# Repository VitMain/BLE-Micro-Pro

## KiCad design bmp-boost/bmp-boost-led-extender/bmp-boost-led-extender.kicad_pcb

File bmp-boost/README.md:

# BMP Boost

## 概要

BMP Boostは、DC-DC昇圧コンバータを搭載したnRF52開発ボードです。電池一本（0.7V以上）で動作可能で、キーボードやその他の低消費電力ワイヤレスプロジェクト向けに設計されています。

ZMK FirmwareやBLE Micro Pro用のファームウェアで動作します。

- [BOOTH](https://nogikes.booth.pm/items/1177319)
- [遊舎工房](https://shop.yushakobo.jp/products/10737)

## 特徴

- DC-DC昇圧コンバータ内蔵で電池一本（0.7V～）から動作可能
- ZMKまたはBLE Micro Pro用のQMKで動作可能
- 追加IOが必要な場合は、コンスルーのピンを差し替えて一部をハーフピッチにして拡張可能（ZMKのみ）

## ピン配置

### 電源コネクタ

| ラベル | 機能                                   |
| ------ | -------------------------------------- |
| BT     | 電源入力(0.7~3.3V)、AIN4で電圧測定可能 |
| G      | 電源入力GND                            |

### Pro Micro互換コネクタ

| ピン番号 | ラベル | GPIO番号 | 機能                                          |
| -------- | ------ | -------- | --------------------------------------------- |
| 1        | 8      | P0.08    | GPIO                                          |
| 2        | 11     | P0.11    | GPIO                                          |
| 3        | GND    |          | GND                                           |
| 4        | GND    |          | GND                                           |
| 5        | 18     | P0.18    | GPIO                                          |
| 6        | 16     | P0.16    | GPIO                                          |
| 7        | 19     | P0.19    | GPIO                                          |
| 8        | 20     | P0.20    | GPIO                                          |
| 9        | 22     | P0.22    | GPIO                                          |
| 10       | 23     | P0.23    | GPIO                                          |
| 11       | 32     | P1.00    | GPIO                                          |
| 12       | 35     | P1.03    | GPIO                                          |
| 13       | 9      | P0.09    | GPIO                                          |
| 14       | 10     | P0.10    | GPIO                                          |
| 15       | 47     | P1.15    | GPIO                                          |
| 16       | 46     | P1.14    | GPIO                                          |
| 17       | 3/A1   | P0.03    | GPIO/AIN1                                     |
| 18       | 30/A6  | P0.30    | GPIO/AIN6                                     |
| 19       | 0      | P0.00    | GPIO                                          |
| 20       | 5/A3   | P0.05    | GPIO/AIN3                                     |
| 21       | VCC    |          | VCC出力(約2.4V *1)                              |
| 22       | BOOT   |          | GNDに落として電源を入れるとブートローダを起動 |
| 23       | GND    |          | GND                                           |
| 24       | 5V     |          | 電源入出力(5V)                                |

\*1 VCC出力にLED（WS2812など）が接続されていると消費電力が著しく増加します。
LEDを実装しないか、実装してしまっている場合はコンスルーのピンを抜いて接続しないようにしてください。
また、起動電流が大きいデバイスを接続している場合、昇圧動作がうまく始まらない場合があります。

### 追加IO

| ラベル | GPIO番号 | 機能    |
| ------ | -------- | ------- |
| VBUS   |          | USB電源 |
| D-     |          | USBのD- |
| D+     |          | USBのD+ |
| 17     | P0.17    | GPIO    |
| 21     | P0.21    | GPIO    |
| 24     | P0.24    | GPIO    |
| 34     | P1.02    | GPIO    |
| 42     | P1.10    | GPIO    |
| 43     | P1.11    | GPIO    |
| 29     | P0.29    | GPIO    |
| 31     | P0.31    | GPIO    |

## ZMK用コンポーネント

- [zmk-component-bmp-boost](https://github.com/sekigon-gonnoc/zmk-component-bmp-boost)
- [QMK用のinfo.jsonをZMK用の設定に変更するツール](https://sekigon-gonnoc.github.io/bmp-qmk-zmk-converter/)
  - 変換結果が正しいとは限らないので適宜修正してください

## 注意事項

- BMPと違いI2Cのレベル変換機能はありません。
- BMPとは電源ピン（VCC）の機能が異なります。
- 仕様等は予告なく変更となる場合があります。

## BMP Boost用拡張ボード

### bmp-boost-extender

[KiCADプロジェクトデータ](./bmp-boost-extender/)

追加IOポートを利用してBMP Boostの背面に搭載できる単四電池基板です。
オプションとしてFFC変換基板を取り付けることもできます。

|        |          |
| -------------------------------- | ------------------------------------- |
|  |  |

### BMP Boost Extender Mini

[リポジトリ](https://github.com/ngsyst/bmp_boost_extender_mini)

ngsystさんが公開している小型の拡張基板です。FFCコネクタがハンダ付けされておりトラックボールやトラックパッドモジュール、エンコーダと接続可能です。

### bmp-boost-led-extender

[KiCADプロジェクトデータ](./bmp-boost-led-extender/)

緑・黄・赤の三色のLEDを追加する拡張基板です。本基板もFFCケーブルで拡張モジュールを接続できます。

### デバイスツリーの例

オプションのFFC変換基板を使用して[paw3222センサ](https://github.com/sekigon-gonnoc/small-mouse-sensor-module)と接続する場合は下記をデバイスツリーに追加してください。

```dts
&pinctrl {
    spi0_default: spi0_default {
        group1 {
            psels = <NRF_PSEL(SPIM_SCK, 0, 17)>,
                <NRF_PSEL(SPIM_MOSI, 0, 21)>,
                <NRF_PSEL(SPIM_MISO, 0, 21)>;
        };
    };

    spi0_sleep: spi0_sleep {
        group1 {
            psels = <NRF_PSEL(SPIM_SCK, 0, 17)>,
                <NRF_PSEL(SPIM_MOSI, 0, 21)>,
                <NRF_PSEL(SPIM_MISO, 0, 21)>;
            low-power-enable;
        };
    };
}

&spi0 {
    status = "okay";
    compatible = "nordic,nrf-spim";
    pinctrl-0 = <&spi0_default>;
    pinctrl-1 = <&spi0_sleep>;
    pinctrl-names = "default", "sleep";
    cs-gpios = <&gpio0 31 GPIO_ACTIVE_LOW>;

    trackball: trackball@0 {
        status = "okay";
        compatible = "pixart,paw3222";
        reg = <0>;
        spi-max-frequency = <2000000>;
        irq-gpios = <&gpio0 29 GPIO_ACTIVE_LOW>;
        power-gpios = <&gpio0 24 (GPIO_ACTIVE_HIGH | NRF_GPIO_DRIVE_H1)>;
    };
};
```

KiCadで作成した基板の設計データは[こちら](bmp-boost-extender/)

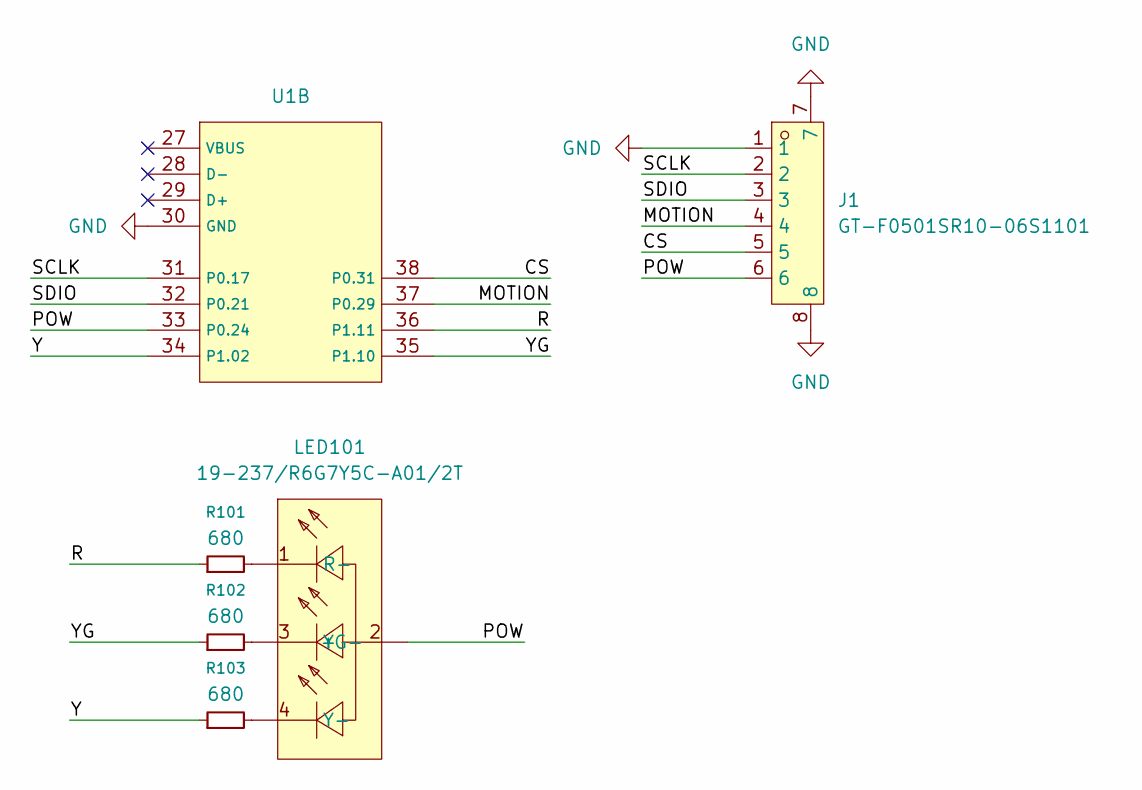
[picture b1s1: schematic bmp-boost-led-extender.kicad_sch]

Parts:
J1: GT-F0501SR10-06S1101; FPC-SMD_6P-P0.50_GT-F0501SR10-06S1101; LCSC Part C22380676
LED101: 19-237/R6G7Y5C-A01/2T; LED-ARRAY-SMD_4P-L1.6-W1.6-BL-CW; LCSC Part C264510
R101, R102, R103: 680; R_0603_1608Metric
U1: BMP-Boost-full

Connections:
/CS: J1.5, U1.38 (P0.31)
/MOTION: J1.4, U1.37 (P0.29)
/POW: J1.6, LED101.2 (+), U1.33 (P0.24)
/R: R101.1, U1.36 (P1.11)
/SCLK: J1.2, U1.31 (P0.17)
/SDIO: J1.3, U1.32 (P0.21)
/Y: R103.1, U1.34 (P1.02)
/YG: R102.1, U1.35 (P1.10)
GND: J1.1, J1.7, J1.8, U1.30 (GND)
unnamed: LED101.1 (R-), R101.2
unnamed: LED101.4 (Y-), R103.2
unnamed: LED101.3 (YG-), R102.2

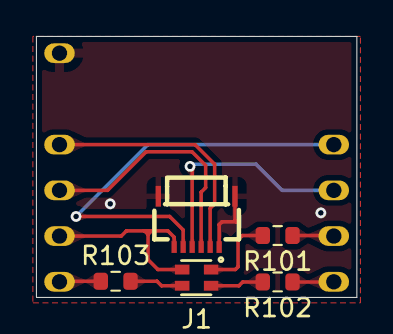
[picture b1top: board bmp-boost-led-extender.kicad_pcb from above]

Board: 2 copper layers, 17.8 x 14.5 mm, 6 parts (0 on the bottom side), 12 nets.

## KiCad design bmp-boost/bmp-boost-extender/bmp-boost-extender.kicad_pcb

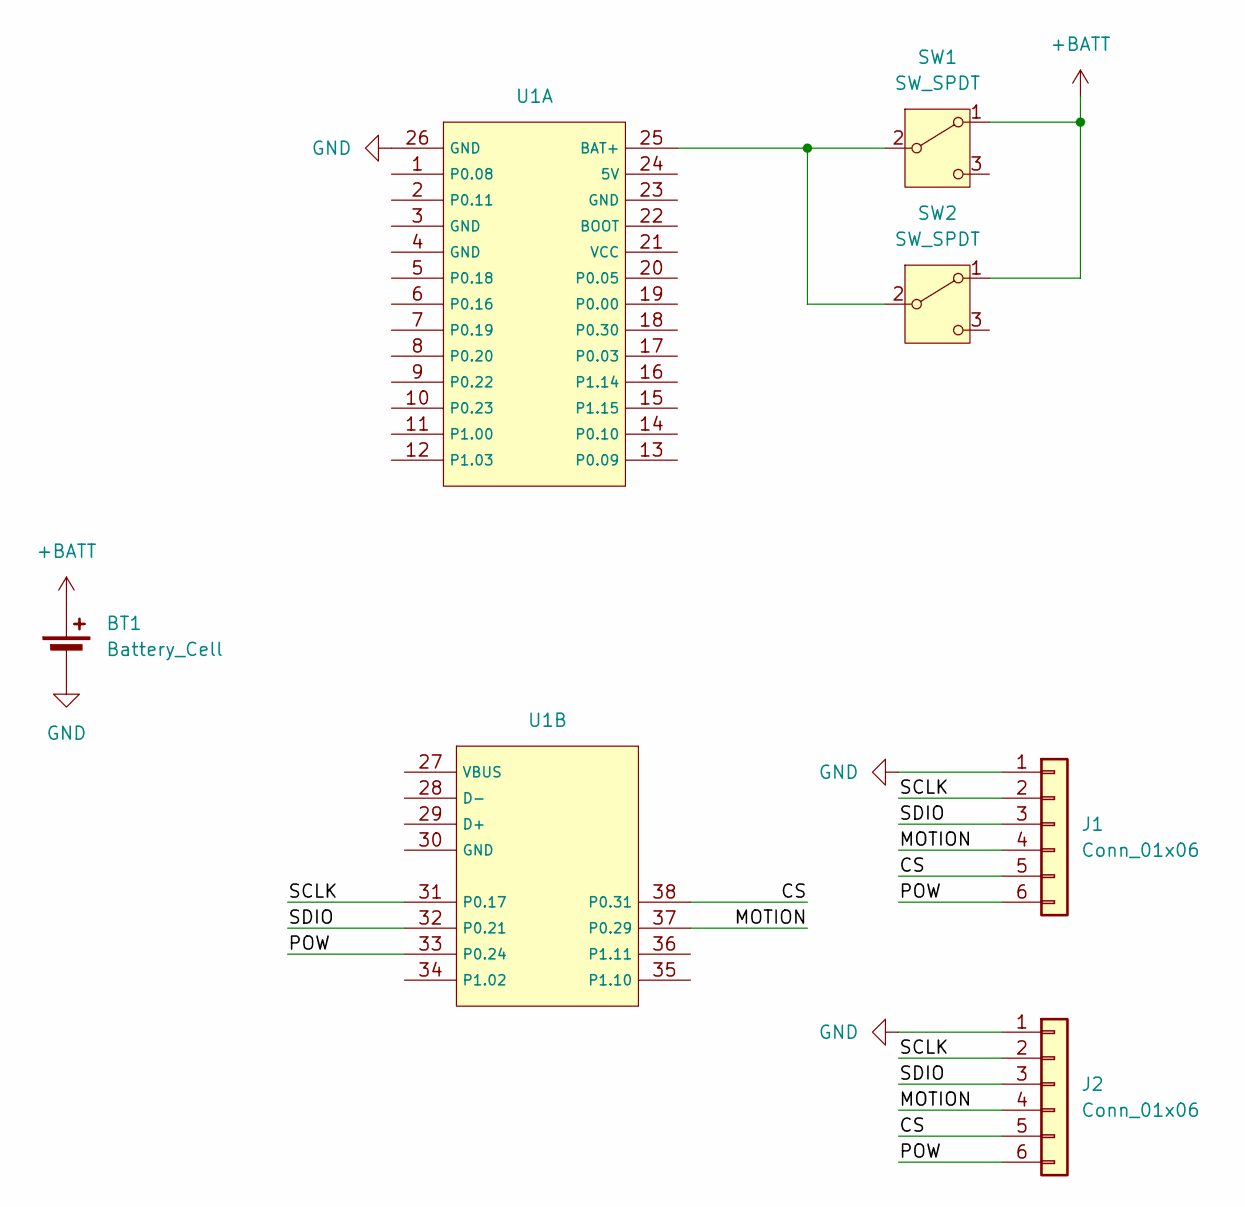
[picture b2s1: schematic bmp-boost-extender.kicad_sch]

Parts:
BT1: Battery_Cell; AAA_Battery_DIP
J1, J2: Conn_01x06; ffc-6p-adapter
SW1, SW2: SW_SPDT; ISH-1260-HA-G
U1: BMP-Boost-full

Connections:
+BATT: BT1.1 (+), SW1.1 (A), SW2.1 (A)
/CS: J1.5, J2.5, U1.38 (P0.31)
/MOTION: J1.4, J2.4, U1.37 (P0.29)
/POW: J1.6, J2.6, U1.33 (P0.24)
/SCLK: J1.2, J2.2, U1.31 (P0.17)
/SDIO: J1.3, J2.3, U1.32 (P0.21)
GND: BT1.2 (-), J1.1, J2.1, U1.26 (GND)
unnamed: SW1.2 (B), SW2.2 (B), U1.25 (BAT+)

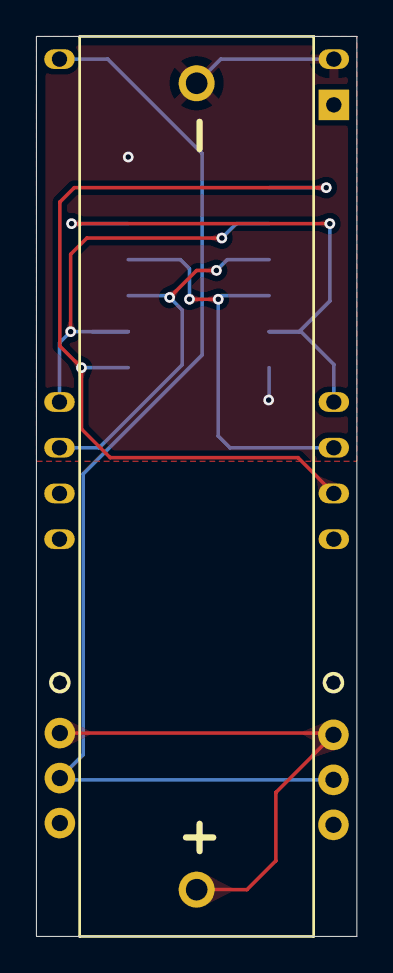
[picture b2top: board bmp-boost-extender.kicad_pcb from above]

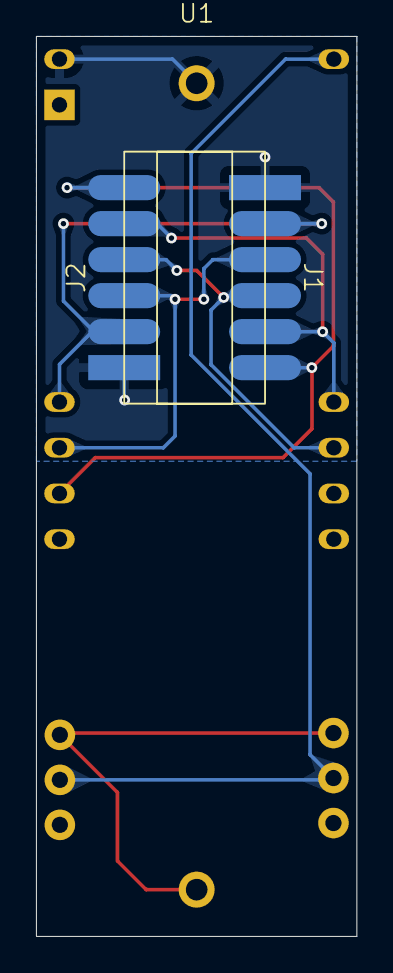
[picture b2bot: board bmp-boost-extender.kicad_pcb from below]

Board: 2 copper layers, 17.8 x 50.0 mm, 6 parts (4 on the bottom side), 8 nets.

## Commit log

2025-09-23 Add bmp-boost KiCad symbols
2025-12-13 Add bmp-boost extender
2026-06-03 bmp-boost-led-extenderを追加
